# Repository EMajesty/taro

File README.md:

# taro

An attempt at a macropad 

## features

* MX/Alps compatible
* 15 buttons
* 1 encoder
* Header for I2C pins

## todo

- [ ] case
- [ ] qmk
- [ ] via
- [ ] things
- [ ] stuff

## parts

| Qty | Thing |
| --- | --- |
| 15 | Switches |
| 1 | EC11 encoder |
| 16 | Diodes |
| 1 | Arduino Pro Micro |
| 1 | Pcb |
| some | bolts |
| and | acrylic |

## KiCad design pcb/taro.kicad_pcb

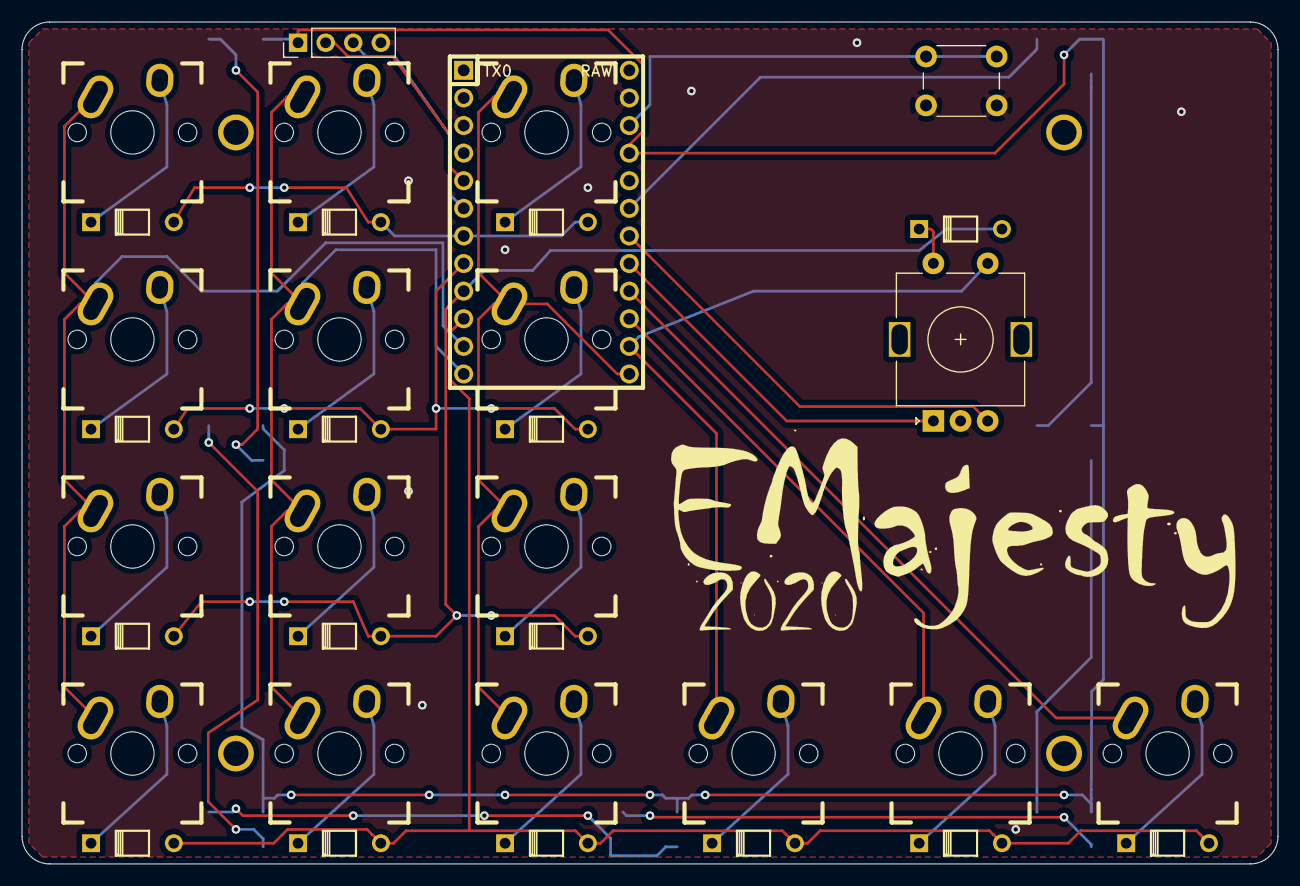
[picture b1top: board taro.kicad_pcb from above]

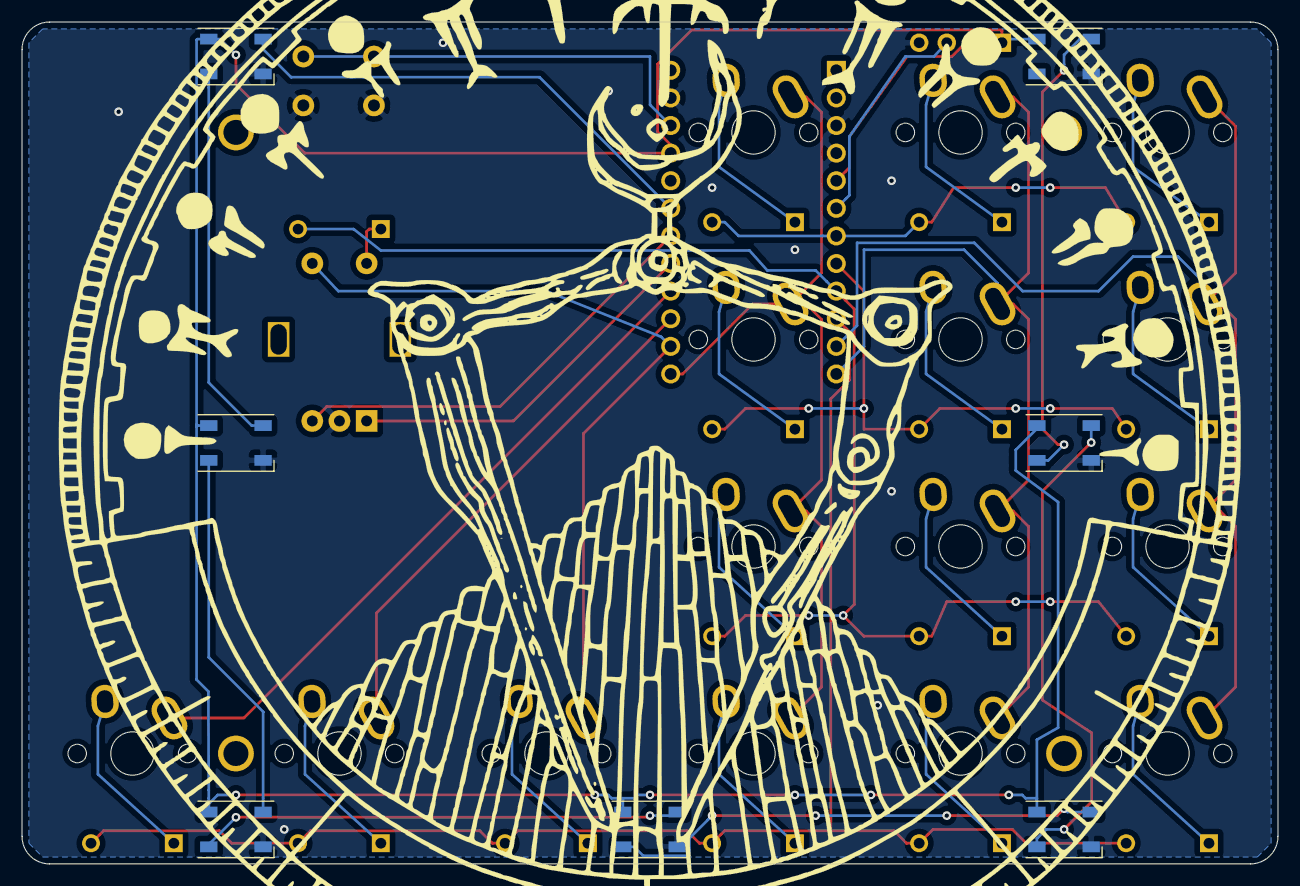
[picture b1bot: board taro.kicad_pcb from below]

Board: 2 copper layers, 115.6 x 77.5 mm, 46 parts (7 on the bottom side), 40 nets.

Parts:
D1, D2, D3, D4, D5, D6, D7, D8, D9, D10, D11, D12, D13, D14, D15, D16: D; Diode
D17, D18, D19, D20, D21, D22, D23: WS2812B; LED_WS2812B-PLCC4
H1, H2, H3, H4: MountingHole; MountingHole_M2
J1: Conn_01x04_Female; Pin_Header_Straight_1x04_Pitch2.54mm
SW1: Reset; SW_PUSH_6mm
SW2, SW3, SW4, SW5, SW6, SW7, SW8, SW9, SW10, SW11, SW12, SW13, SW14, SW15, SW16: SW_Push; Hybrid_PCB_100H
SW17: Rotary_Encoder_Switch; RotaryEncoder_Alps_EC11E-Switch_Vertical_H20mm
U1: ProMicro; ArduinoProMicro-TopSide

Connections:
/COL_A: SW2.1, SW3.1, SW4.1, SW5.1, U1.11
/COL_B: SW6.1, SW7.1, SW8.1, SW9.1, U1.12
/COL_C: SW10.1, SW11.1, SW12.1, SW13.1, U1.13
/COL_D: SW14.1, SW17.S1, U1.14
/COL_E: SW15.1, U1.15
/COL_F: SW16.1, U1.16
/LED_IN: D17.4, U1.19
/ROT1_A: SW17.A, U1.17
/ROT1_B: SW17.B, U1.18
/ROW_A: D1.1, D5.1, D9.1, U1.7
/ROW_B: D2.1, D6.1, D10.1, U1.8
/ROW_C: D3.1, D7.1, D11.1, D14.1, U1.9
/ROW_D: D4.1, D8.1, D12.1, D13.1, D15.1, D16.1, U1.10
/SCL: J1.2, U1.5
/SDA: J1.3, U1.6
GND: D17.3, D18.3, D19.3, D20.3, D21.3, D22.3, D23.3, J1.4, SW1.2, SW17.C, U1.3, U1.4, U1.23
unnamed: D1.2, SW2.2
unnamed: D2.2, SW3.2
unnamed: D3.2, SW4.2
unnamed: D4.2, SW5.2
unnamed: D5.2, SW6.2
unnamed: D6.2, SW7.2
unnamed: D7.2, SW8.2
unnamed: D8.2, SW9.2
unnamed: D9.2, SW10.2
unnamed: D10.2, SW11.2
unnamed: D11.2, SW12.2
unnamed: D12.2, SW13.2
unnamed: D13.2, SW14.2
unnamed: D14.2, SW17.S2
unnamed: D15.2, SW15.2
unnamed: D16.2, SW16.2
unnamed: D17.2, D18.4
unnamed: D18.2, D19.4
unnamed: D19.2, D20.4
unnamed: D20.2, D21.4
unnamed: D21.2, D22.4
unnamed: D22.2, D23.4
unnamed: SW1.1, U1.22
VCC: D17.1, D18.1, D19.1, D20.1, D21.1, D22.1, D23.1, J1.1, U1.21

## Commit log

2020-09-10 commit message
2020-09-10 Added mounting holes
2020-09-10 template pngs
2020-09-10 add taro
2020-09-10 image embed
2020-09-10 folder for pics
2020-09-10 rename pcb folder
2020-09-10 case
2020-09-11 pcb ready for art
2020-09-11 art into gerbers
2020-09-11 more gerber art
2020-09-11 asdf
2020-09-12 en tiiä
2020-09-12 vectorized top art
2020-09-12 vector into mod
2020-09-12 vector
2020-09-12 vectors
2020-09-12 vectorz
2020-09-12 top art mod
2020-09-13 pcb done?
2020-09-13 pcb done
2020-09-13 pcb folder cleanup
2020-09-13 pcb cleanup
2020-09-13 updated gitignore
2020-09-15 readme
2020-11-03 proge
2021-04-06 remove personal bom
